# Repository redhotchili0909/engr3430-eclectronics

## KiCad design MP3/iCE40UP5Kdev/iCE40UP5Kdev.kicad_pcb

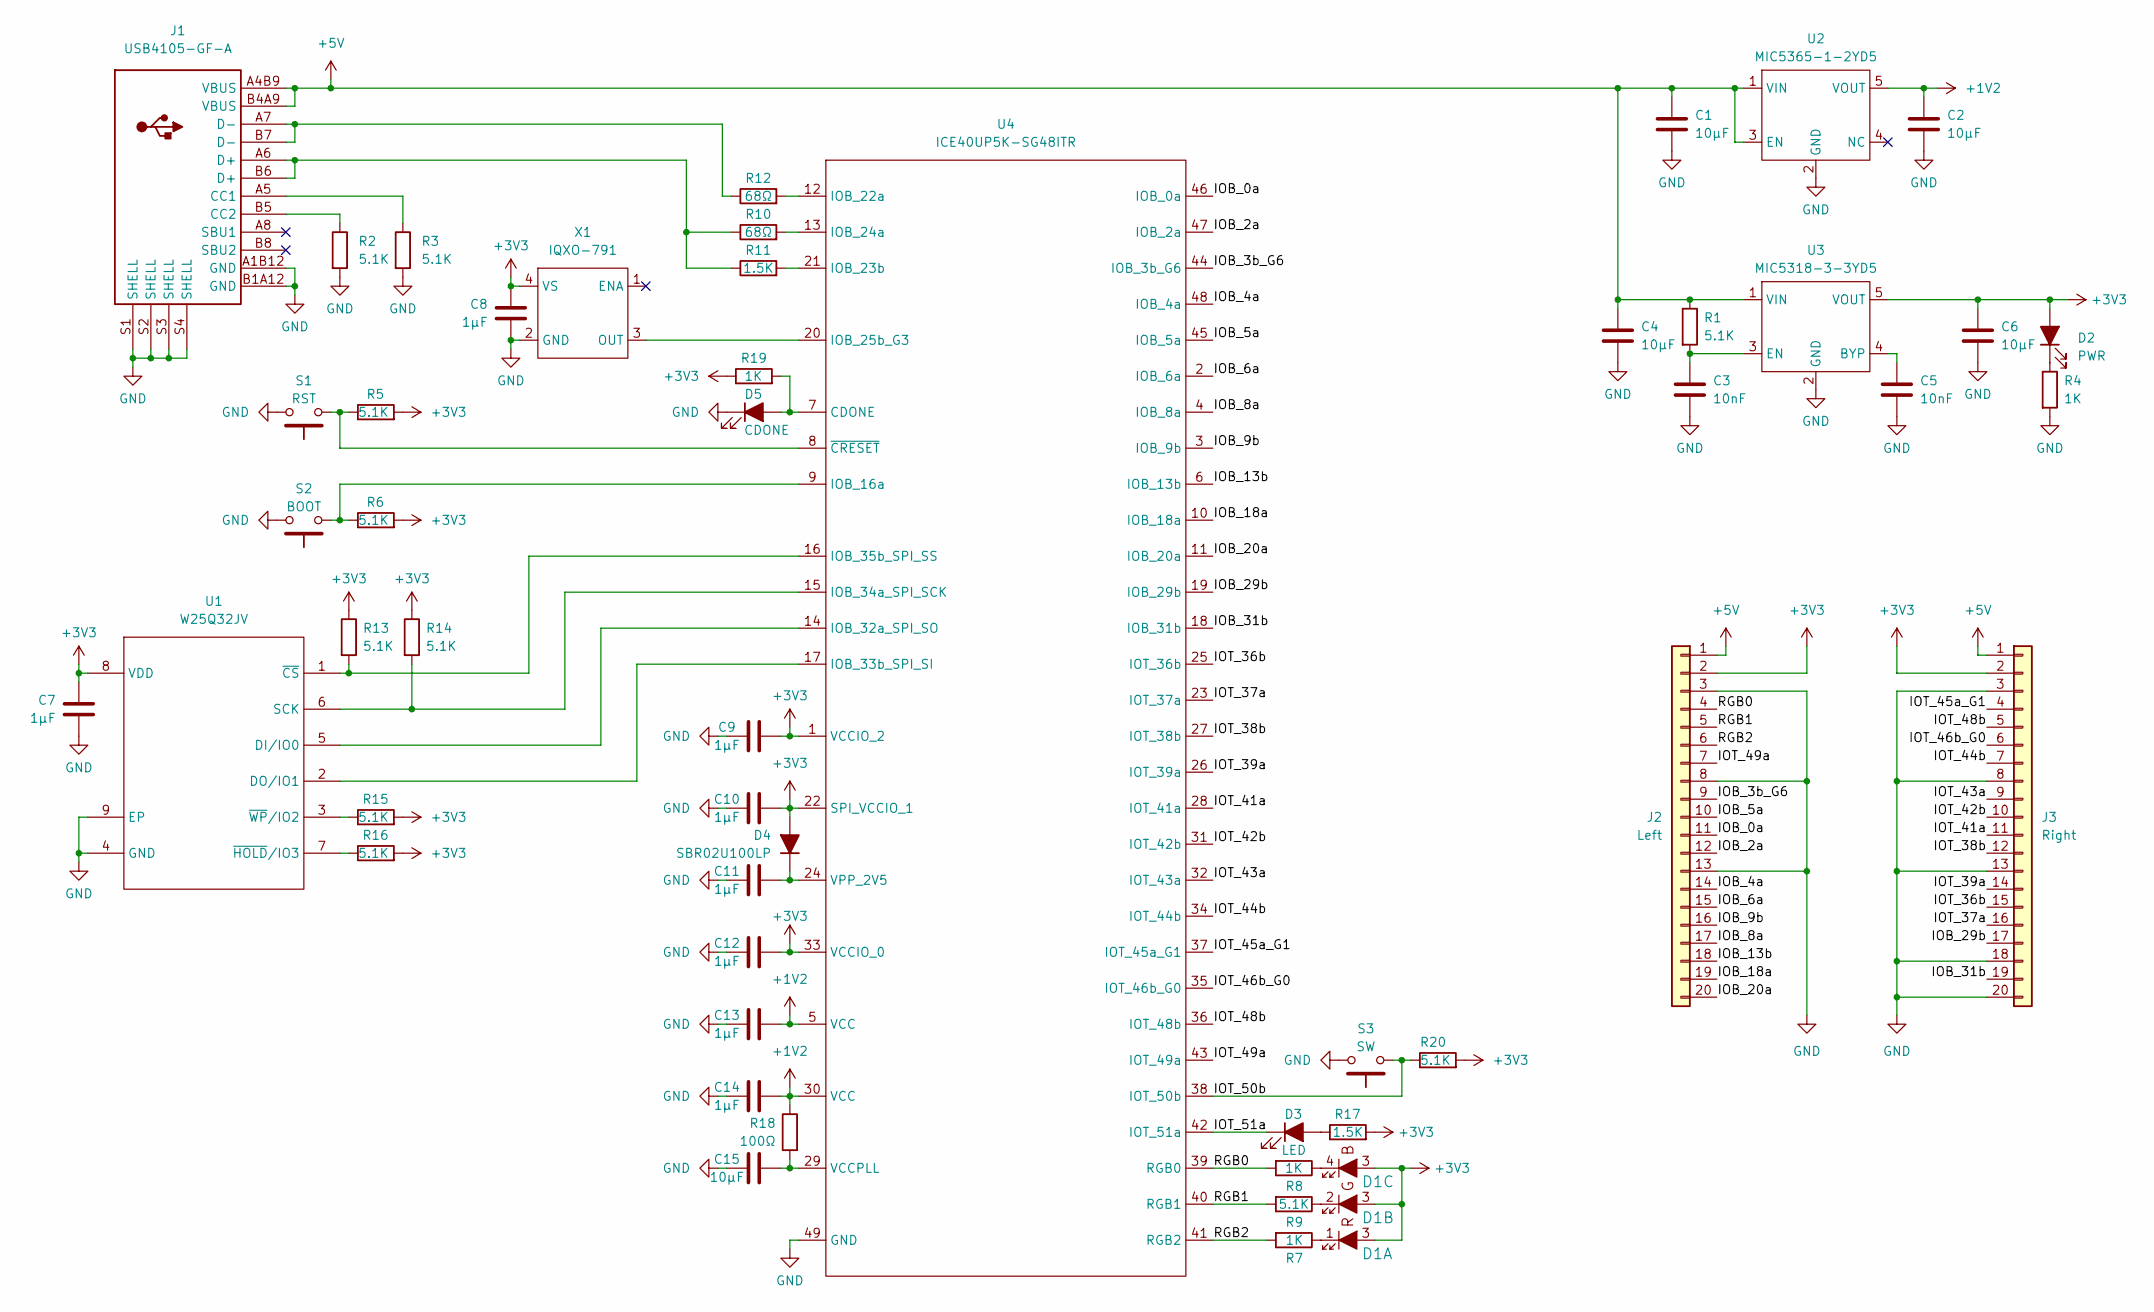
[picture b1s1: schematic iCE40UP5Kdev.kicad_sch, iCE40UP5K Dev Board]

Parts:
C1, C2, C4, C6, C15: 10µF; C_0603_1608Metric
C3, C5: 10nF; C_0402_1005Metric
C7, C8, C9, C10, C11, C12, C13, C14: 1µF; C_0402_1005Metric
D1: IN-S85TATRGB_ALT; IN-S85TATRGB
D2: PWR; LED_0805_2012Metric
D3: LED; LED_0805_2012Metric
D4: SBR02U100LP; D_0402_1005Metric
D5: CDONE; LED_0805_2012Metric
J1: USB4105-GF-A
J2: Left; PinHeader_1x20_P2.54mm_Vertical
J3: Right; PinHeader_1x20_P2.54mm_Vertical
R1, R2, R3, R5, R6, R9, R13, R14, R15, R16, R20: 5.1K; R_0402_1005Metric
R4, R7, R8, R19: 1K; R_0402_1005Metric
R10, R12: 68Ω; R_0402_1005Metric
R11, R17: 1.5K; R_0402_1005Metric
R18: 100Ω; R_0402_1005Metric
S1: RST; SW_SPST_B3U-1000P
S2: BOOT; SW_SPST_B3U-1000P
S3: SW; SW_SPST_B3U-1000P
U1: W25Q32JV; WSON-8-1EP_6x5mm_P1.27mm_EP3.4x4.3mm
U2: MIC5365-1-2YD5; TSOT-23-5
U3: MIC5318-3-3YD5; TSOT-23-5
U4: ICE40UP5K-SG48ITR; QFN-48-1EP_7x7mm_P0.5mm_EP5.6x5.6mm
X1: IQXO-791

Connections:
+1V2: C2.1, C13.2, C14.2, R18.1, U2.5 (VOUT), U4.5 (VCC), U4.30 (VCC)
+3V3: C6.1, C7.1, C8.1, C9.2, C10.2, C12.2, D1.3, D2.2 (A), D4.2 (A), J2.2, J3.2, R5.2, R6.2, R13.1, R14.1, R15.2, R16.2, R17.2, R19.1, R20.2, U1.8 (VDD), U3.5 (VOUT), U4.1 (VCCIO_2), U4.22 (SPI_VCCIO_1), U4.33 (VCCIO_0), X1.4 (VS)
+5V: C1.1, C4.1, J1.A4B9 (VBUS), J1.B4A9 (VBUS), J2.1, J3.1, R1.1, U2.1 (VIN), U2.3 (EN), U3.1 (VIN)
/IOB_0a: J2.11, U4.46 (IOB_0a)
/IOB_2a: J2.12, U4.47 (IOB_2a)
/IOB_3b_G6: J2.9, U4.44 (IOB_3b_G6)
/IOB_4a: J2.14, U4.48 (IOB_4a)
/IOB_5a: J2.10, U4.45 (IOB_5a)
/IOB_6a: J2.15, U4.2 (IOB_6a)
/IOB_8a: J2.17, U4.4 (IOB_8a)
/IOB_9b: J2.16, U4.3 (IOB_9b)
/IOB_13b: J2.18, U4.6 (IOB_13b)
/IOB_18a: J2.19, U4.10 (IOB_18a)
/IOB_20a: J2.20, U4.11 (IOB_20a)
/IOB_29b: J3.17, U4.19 (IOB_29b)
/IOB_31b: J3.19, U4.18 (IOB_31b)
/IOT_36b: J3.15, U4.25 (IOT_36b)
/IOT_37a: J3.16, U4.23 (IOT_37a)
/IOT_38b: J3.12, U4.27 (IOT_38b)
/IOT_39a: J3.14, U4.26 (IOT_39a)
/IOT_41a: J3.11, U4.28 (IOT_41a)
/IOT_42b: J3.10, U4.31 (IOT_42b)
/IOT_43a: J3.9, U4.32 (IOT_43a)
/IOT_44b: J3.7, U4.34 (IOT_44b)
/IOT_45a_G1: J3.4, U4.37 (IOT_45a_G1)
/IOT_46b_G0: J3.6, U4.35 (IOT_46b_G0)
/IOT_48b: J3.5, U4.36 (IOT_48b)
/IOT_49a: J2.7, U4.43 (IOT_49a)
/IOT_50b: R20.1, S3.1, U4.38 (IOT_50b)
/IOT_51a: D3.1 (K), U4.42 (IOT_51a)
/RGB0: J2.4, R8.2, U4.39 (RGB0)
/RGB1: J2.5, R9.2, U4.40 (RGB1)
/RGB2: J2.6, R7.2, U4.41 (RGB2)
GND: C1.2, C2.2, C3.2, C4.2, C5.2, C6.2, C7.2, C8.2, C9.1, C10.1, C11.1, C12.1, C13.1, C14.1, C15.1, D5.1 (K), J1.A1B12 (GND), J1.B1A12 (GND), J1.S1 (SHELL), J1.S2 (SHELL), J1.S3 (SHELL), J1.S4 (SHELL), J2.3, J2.8, J2.13, J3.3, J3.8, J3.13, J3.18, J3.20, R2.2, R3.2, R4.2, S1.2, S2.2, S3.2, U1.4 (GND), U1.9 (EP), U2.2 (GND), U3.2 (GND), U4.49 (GND), X1.2 (GND)
unnamed: D1.1, R7.1
unnamed: D1.2, R9.1
unnamed: D1.4, R8.1
unnamed: D2.1 (K), R4.1
unnamed: D3.2 (A), R17.1
unnamed: C11.2, D4.1 (K), U4.24 (VPP_2V5)
unnamed: D5.2 (A), R19.2, U4.7 (CDONE)
unnamed: J1.A5 (CC1), R3.1
unnamed: J1.B5 (CC2), R2.1
unnamed: J1.A6 (D+), J1.B6 (D+), R10.1, R11.1
unnamed: J1.A7 (D-), J1.B7 (D-), R12.1
unnamed: U1.5 (DI/IO0), U4.14 (IOB_32a_SPI_SO)
unnamed: U1.2 (DO/IO1), U4.17 (IOB_33b_SPI_SI)
unnamed: R14.2, U1.6 (SCK), U4.15 (IOB_34a_SPI_SCK)
unnamed: R13.2, U1.1 (~CS), U4.16 (IOB_35b_SPI_SS)
unnamed: R16.1, U1.7 (~HOLD/IO3)
unnamed: R15.1, U1.3 (~WP/IO2)
unnamed: C5.1, U3.4 (BYP)
unnamed: C3.1, R1.2, U3.3 (EN)
unnamed: R6.1, S2.1, U4.9 (IOB_16a)
unnamed: R12.2, U4.12 (IOB_22a)
unnamed: R11.2, U4.21 (IOB_23b)
unnamed: R10.2, U4.13 (IOB_24a)
unnamed: U4.20 (IOB_25b_G3), X1.3 (OUT)
unnamed: C15.2, R18.2, U4.29 (VCCPLL)
unnamed: R5.1, S1.1, U4.8 (~CRESET)

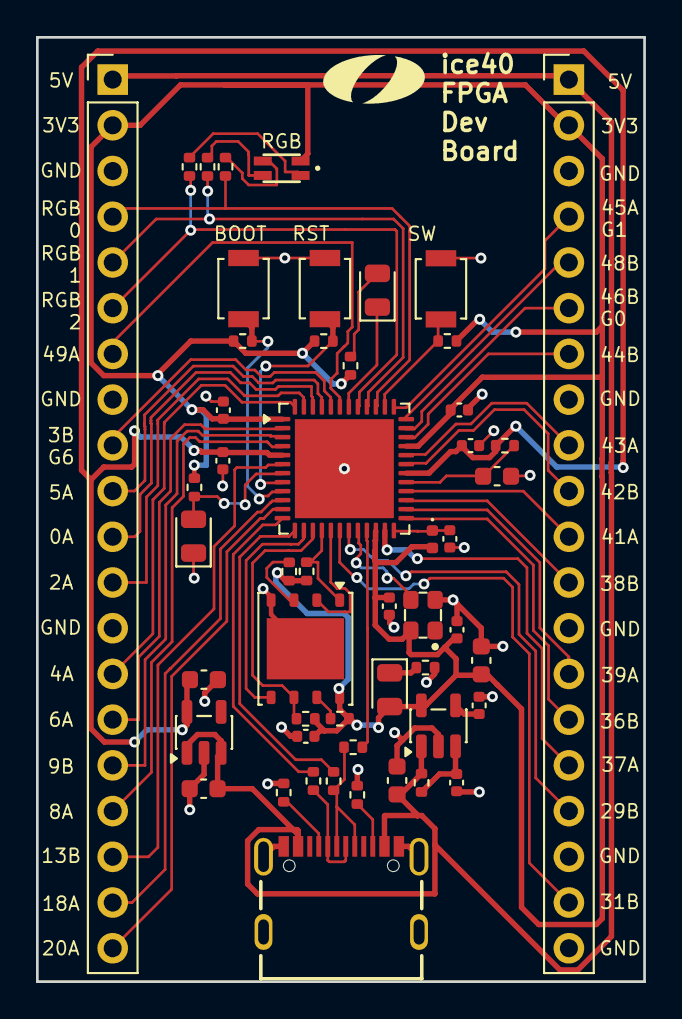
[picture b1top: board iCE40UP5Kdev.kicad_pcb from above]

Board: 2 copper layers, 33.7 x 52.5 mm, 52 parts (0 on the bottom side), 60 nets.

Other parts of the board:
OlinLogo: G***; OlinLogo

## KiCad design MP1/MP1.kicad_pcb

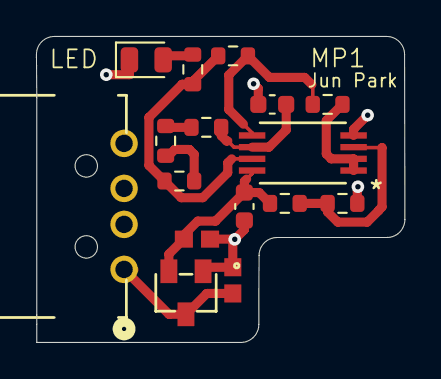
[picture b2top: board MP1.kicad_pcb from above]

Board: 2 copper layers, 20.5 x 17.0 mm, 16 parts (0 on the bottom side), 11 nets.

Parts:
C1, C2: 1uF; CAPC17595_95N_KEM
C3, C4: 0.1uF; C_0603_1608Metric
D1: LED; LED_0805_2012Metric
J1: USB_A; CONN_480370001_MOL
R1, R2, R3, R5, R7: 10k; R_0603_1608Metric
R4: 1M; R_0603_1608Metric
R6: 3.01M; R_0603_1608Metric
R8: 499k; R_0603_1608Metric
U1: MCP1702T-3302E/CB; SOT-23A_MC_MCH
U4: MCP6022T-I/ST; TSSOP8_MC_MCH

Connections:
+5V: C1.1, J1.1 (VBUS), U1.3 (VIN)
/LED_VIN: R3.2, R7.2, R8.2, U4.7 (VOUTB)
/VDD: C2.1, C4.1, R1.1, U1.2 (VOUT), U4.8 (VDD)
/VINA+: R1.2, R2.1, U4.3 (VINA+)
/VINB+: R5.2, R7.1, U4.5 (VINB+)
/VINB-: C3.1, R6.1, U4.6 (VINB-)
/VREF: R5.1, U4.1 (VOUTA), U4.2 (VINA-)
GND: C1.2, C2.2, C3.2, C4.2, D1.1 (K), J1.4 (GND), R2.2, U1.1 (GND), U4.4 (VSS)
unnamed: D1.2 (A), R3.1
unnamed: R4.1, R6.2
unnamed: R4.2, R8.1

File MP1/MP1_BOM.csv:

Reference,Qty,Value,Footprint,Datasheet,Manufacturer Part #
"C1,C2",2,1uF,MP1-footprints:CAPC17595_95N_KEM,https://www.digikey.com/en/products/detail/kemet/C0603C105K3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,C0603C105K3RACTU
"C3,C4",2,0.1uF,Capacitor_SMD:C_0603_1608Metric,https://www.digikey.com/en/products/detail/yageo/CC0603JRX7R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,CC0603JRX7R9BB104
D1,1,LED,LED_SMD:LED_0805_2012Metric,https://optoelectronics.liteon.com/upload/download/DS-22-99-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,LTST-C170TBKT
J1,1,USB_A,MP1-footprints:CONN_480370001_MOL,https://www.digikey.com/en/products/detail/molex/0480370001/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,0480370001
"R1,R2,R3,R5,R7",5,10k,Resistor_SMD:R_0603_1608Metric,https://www.digikey.com/en/products/detail/yageo/RC0603FR-07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,RC0603FR-0710KL
R4,1,1M,Resistor_SMD:R_0603_1608Metric,https://www.digikey.com/en/products/detail/yageo/RC0603FR-07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,RC0603FR-071ML
R6,1,3.01M,Resistor_SMD:R_0603_1608Metric,https://www.digikey.com/en/products/detail/yageo/RC0603FR-07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,RC0603FR-073M01L
R8,1,499k,Resistor_SMD:R_0603_1608Metric,https://www.digikey.com/en/products/detail/yageo/RC0603FR-07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,RC0603FR-07499KL
U1,1,MCP1702T-3302E/CB,MP1-footprints:SOT-23A_MC_MCH,https://ww1.microchip.com/downloads/en/DeviceDoc/22008E.pdf,MCP1702T-3302E/CB
U4,1,MCP6022T-I/ST,MP1-footprints:TSSOP8_MC_MCH,https://ww1.microchip.com/downloads/en/DeviceDoc/20001685E.pdf,MCP6022T-I/ST

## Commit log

2026-02-09 MP1 Submission
2026-02-09 Add Assignment PDF
2026-02-09 Edit Typo
2026-03-02 Add MP3
2026-03-03 Rev.1 Layout
2026-03-08 Final Design with PinHeader Labels + Graphics
2026-03-08 MP3 Final Edit
    - Added Graphics
    - Labels for Pin Headers
2026-03-09 Implementing Feedback
    - Made USB D+, D- on one plane and made the path shorter
    - Used correct footprint for FPGA Chip
2026-03-09 Modify .gitignore
